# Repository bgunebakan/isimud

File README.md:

# Isimud
Sattellite modem control software and web application

# v2
Isimud v2 created with JAVA and Netbeans 8.0.2

# Libraries
 - Commons Cli 1.2
 - Pi4j

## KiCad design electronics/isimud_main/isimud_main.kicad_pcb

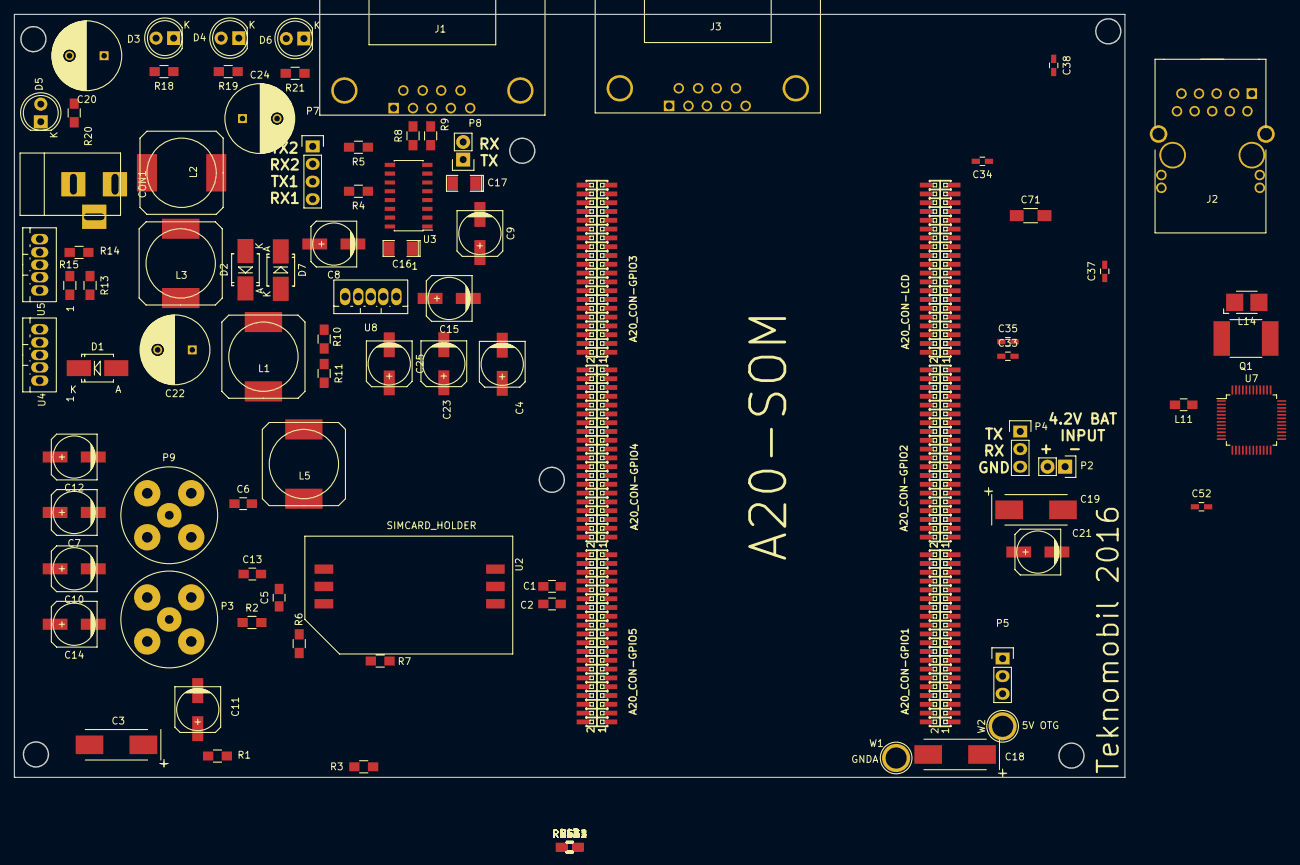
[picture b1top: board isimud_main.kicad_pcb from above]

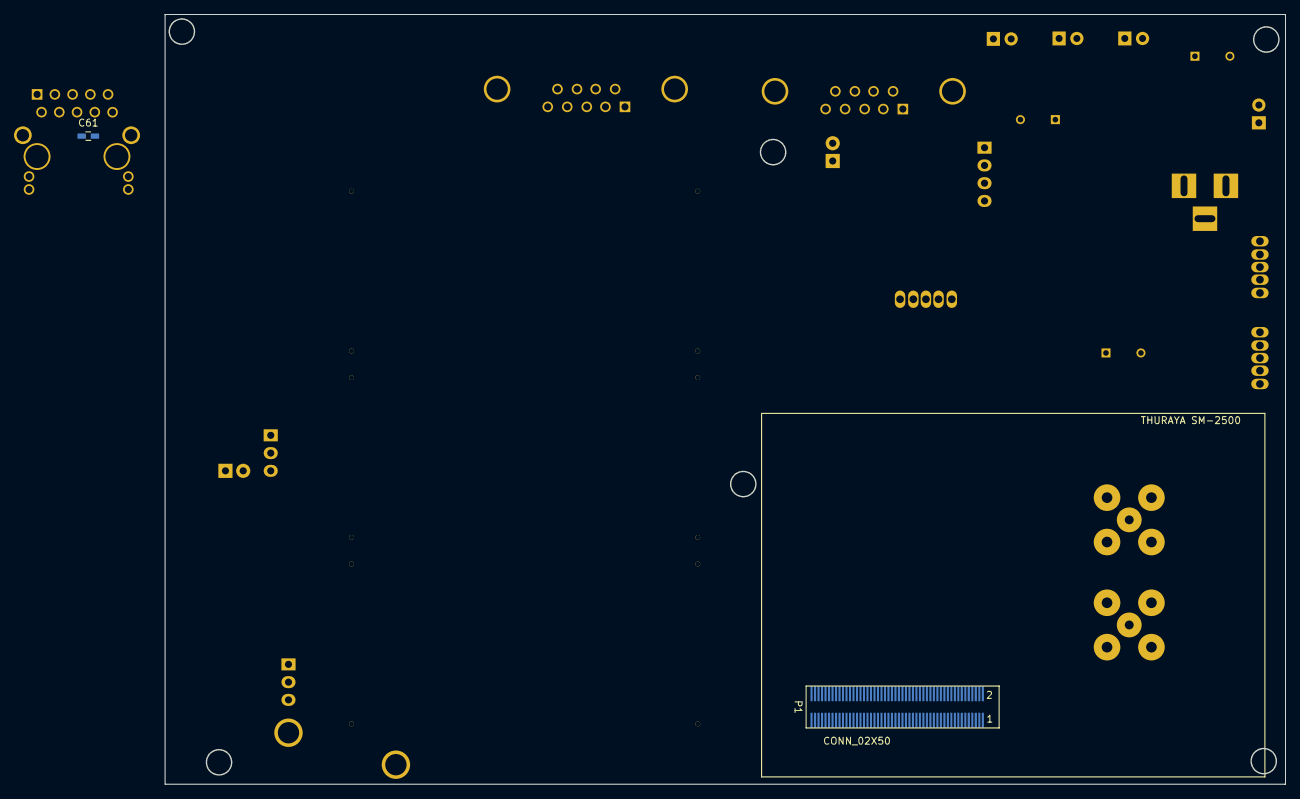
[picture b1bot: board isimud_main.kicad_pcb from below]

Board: 2 copper layers, 160.3 x 110.1 mm, 129 parts (2 on the bottom side), 115 nets, no tracks yet.

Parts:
C1, C2, C5: 33pF; C_0805_HandSoldering
C3: 33uF 16V; TantalC_SizeD_EIA-7343_HandSoldering
C4: 1uF 16V; c_elec_6.3x5.8
C6, C13: 100nF; C_0805_HandSoldering
C7, C10, C11, C12, C14: 47uF 16V; c_elec_6.3x5.8
C8, C9: 1uF; c_elec_6.3x5.8
C15: 100uF; c_elec_6.3x5.8
C16, C17: 1uF; SMD-1206_Pol
C18: 10uF; TantalC_SizeD_EIA-7343_HandSoldering
C19: 22uF 6.3v; TantalC_SizeD_EIA-7343_HandSoldering
C20, C22, C24: 1000uF 16V; C_Radial_D10_L16_P5
C21, C23, C25: 220uF 16V; c_elec_6.3x5.8
C33, C37, C48, C52, C53: 22uF/6.3V; C_0603_HandSoldering
C34, C35, C38, C41, C43, C50, C51, C54, C55, C56, C57, C58, C59, C61: 100nF; C_0603_HandSoldering
C42, C65: NA; C_0603_HandSoldering
C62, C64: 27pF; C_0603_HandSoldering
C71: 1nF/2kV/X7R/1206; C_1206_HandSoldering
CON1: 12V DC; BARREL_JACK
D1, D2, D7: 1N5822; SMB_Handsoldering
D3: SAT_ON; LED-5MM
D4: GPS_ON; LED-5MM
D5: PWR_ON; LED-5MM
D6: STATUS; LED-5MM
J1, J3: DB9; DB9FC
J2: TM211Q01FM22
L1, L2, L3, L5: 100uH; SELF-WE-PD-XXL
L11, L12, L13: FB0805/600R/2A; C_0805_HandSoldering
L14: 4.7uH/1.15A/DCR<0.1R/CD43; Inductor_1212
P1: CONN_02X50; BB-2X50-SMD
P2: LIPO_BAT; Socket_Strip_Straight_1x02
P3: SAT MODULE GPS; bnc-ci
P4: UART_0; Pin_Header_Straight_1x03
P5: UART_4; Pin_Header_Straight_1x03
P7: RS232-UART; Pin_Header_Straight_1x04
P8: RS232-2; Pin_Header_Straight_1x02
P9: AKTIF GPS ANTEN; bnc-ci
Q1: E4SB25.000F20E15(25MHz/20pF/20ppm/5x3.2mm); C_2220_HandSoldering
R1, R2, R8, R9, R11: 0R; R_0805_HandSoldering
R3: 10k; R_0805_HandSoldering
R4, R5: 2k2; R_0805_HandSoldering
R6, R7: 330; R_0805_HandSoldering
R10: NA; R_0805_HandSoldering
R13, R14: 1k2; R_0805_HandSoldering
R15: 1k; R_0805_HandSoldering
R18, R19, R20, R21: 220R; R_0805_HandSoldering
R40: 10K; R_0603_HandSoldering
R41, R42, R66: 22R; R_0603_HandSoldering
R43: 10k; R_0603_HandSoldering
R44, R57, R60, R64: NA; R_0603_HandSoldering
R47, R49, R61: 1K; R_0603_HandSoldering
R48, R59, R62: 4K7; R_0603_HandSoldering
R52: 2.49k/1%; R_0603_HandSoldering
R63: 1k; R_0603_HandSoldering
R65: NA(4.7k); R_0603_HandSoldering
RM4G1, RM4G2, RM4G3: R; R_0603_HandSoldering
RM5G1, RM5G2, RM5G3, RM5G4: RA1206_(4X0603)_4B8_22R; R_0603_HandSoldering
U1: SOM-A20; A20-SOM
U2: SIMCARD_HOLDER; SIMCARD
U3: MAX232; SOIC-16_3.9x9.9mm_Pitch1.27mm
U4, U8: LM2576-5V; Pentawatt_Neutral_Straight_Vertical_TO220-5-T05A
U5: LM2576; Pentawatt_Neutral_Straight_Vertical_TO220-5-T05A
U7: RTL8211CL-GR; LQFP-48_7x7mm_Pitch0.5mm
W1: GNDA; 1pin
W2: 5V OTG; 1pin

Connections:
+3V3: L11.2, L12.2, L13.2, R47.2, R48.2, R49.2, R62.2, RM4G1.2, RM4G2.2, RM4G3.2, U1.3-3, U1.4-3, U1.6-3
+5V: C7.1, C10.1, C12.1, C14.1, C16.2, C18.1, P1.65, P1.93, P1.94, P1.95, P1.96, P1.97, P1.98, P1.99, P1.100, R1.2, R3.2, U1.1-1, U1.3-1, U1.4-1, U1.6-1, U3.16
+5VD: C24.1, C25.1, L2.2, U8.4
+6V: C3.1, C4.1, C22.1, C23.1, L3.2, P1.73, P1.75, P1.77, P1.79, P1.81, R13.2
+12V: C15.1, CON1.1, U4.1, U5.1, U8.1
+BATT: C19.1, P2.2, U1.2-3
/THURAYA_RX: P1.24, R7.2
/THURAYA_TX: P1.22, R6.2
CLK125: R66.2, U1.2-38
EMDIO: R49.1, U7.31
EPHY-RST#: R64.1, U1.2-40
ERXCK: R42.2, U1.2-33
ERXD0: RM5G4.2, U1.2-23
ERXD1: RM5G3.2, U1.2-25
ERXD2: RM5G2.2, U1.2-27
ERXD3: RM5G1.2, U1.2-29
ERXDV: R41.2, U1.2-31
ETXCK: R10.1, R11.1, U7.22
ETXD0: U1.2-24, U7.23
ETXD1: U1.2-26, U7.24
ETXD2: U1.2-28, U7.25
ETXD3: U1.2-30, U7.26
ETXEN: U1.2-32, U7.27
GND: C1.2, C2.2, C3.2, C4.2, C5.2, C7.2, C10.2, C12.2, C14.2, C15.2, C17.1, C18.2, C19.2, C20.2, C21.2, C22.2, C23.2, C24.2, C25.2, C33.1, C34.1, C35.1, C37.1, C38.1, C41.1, C42.1, C43.1, C48.1, C50.1, C51.1, C52.1, C53.1, C54.1, C55.1, C56.1, C57.1, C58.1, C59.2, C61.2, C62.1, C64.1, C65.1, C71.1, CON1.2, CON1.3, D1.2, D2.2, D3.1, D4.1, D5.1, D6.1, D7.2, J1.5, J2.10, J3.5, P1.28, P1.35, P1.50, P1.67, P1.68, P1.69, P1.70, P1.76, P1.82, P1.83, P1.85, P1.86, P1.87, P1.88, P1.89, P1.90, P1.91, P1.92, P2.1, P4.3, P5.3, R2.2, R15.1, R40.2, R44.1, R52.1, R59.1, R60.2, R61.1, R65.2, U1.1-2, U1.2-2, U1.2-4, U1.4-2, U1.5-2, U1.6-2, U1.6-4, U2.4, U3.15, U4.3, U4.5, U5.3, U5.5, U7.7, U7.12, U7.20, U7.33, U7.47, U8.3, U8.5
GNDA: U1.1-4, W1.1
GPS_LED: R19.1, U1.5-9
unnamed: C1.1, P1.62, U2.2
unnamed: C2.1, P1.60, U2.3
unnamed: C5.1, P1.58, U2.6
unnamed: C8.1, U3.1
unnamed: C8.2, U3.3
unnamed: C9.1, U3.4
unnamed: C9.2, U3.5
unnamed: C6.2, C11.1, L5.1, R1.1
unnamed: C6.1, C11.2, P3.2, P9.2, R2.1
unnamed: C13.1, P3.1
unnamed: C13.2, L5.2, P9.1
unnamed: C16.1, U3.2
unnamed: C17.2, U3.6
unnamed: C33.2, C34.2, C35.2, L11.1, U7.6, U7.41
unnamed: C37.2, C38.2, C41.2, C43.2, L12.1, U7.15, U7.21, U7.37
unnamed: C42.2, R42.1, U7.19
unnamed: C48.2, C50.2, C51.2, L13.1, U7.44, U7.45
unnamed: C52.2, C53.2, C54.2, C55.2, C56.2, C57.2, C58.2, L14.2, U7.3, U7.10, U7.28, U7.36, U7.40
unnamed: C59.1, J2.5
unnamed: C61.1, J2.6
unnamed: C62.2, Q1.1, U7.42
unnamed: C64.2, Q1.2, U7.43
unnamed: C65.2, R57.2, R63.2, R64.2, U7.29
unnamed: C71.2, J2.SH1, J2.SH2
unnamed: D1.1, L1.1, U4.2
unnamed: D2.1, L3.1, U5.2
unnamed: D3.2, R18.2
unnamed: D4.2, R19.2
unnamed: D5.2, R20.2
unnamed: D6.2, R21.2
unnamed: D7.1, L2.1, U8.2
unnamed: J1.2, R8.2
unnamed: J1.3, R9.2
unnamed: J2.1, U7.1
unnamed: J2.2, U7.2
unnamed: J2.3, U7.4
unnamed: J2.4, U7.5
unnamed: J2.7, U7.8
unnamed: J2.8, U7.9
unnamed: J2.9, U7.11
unnamed: J2.11, R59.2, U7.35
unnamed: J2.12, R61.2
unnamed: J2.13, R47.1
unnamed: J2.14, R48.1, U7.34
unnamed: L14.1, U7.48
unnamed: P1.64, U2.1
unnamed: P7.3, U3.10
unnamed: P7.4, R5.2
unnamed: P8.1, U3.7
unnamed: P8.2, U3.8
unnamed: R4.1, U3.12
unnamed: R5.1, U3.9
unnamed: R8.1, U3.14
unnamed: R9.1, U3.13
unnamed: R10.2, U1.2-34
unnamed: R11.2, U1.2-36
unnamed: R13.1, R14.1
unnamed: R14.2, R15.2, U5.4
unnamed: R40.1, R41.1, U7.13
unnamed: R43.1, R57.1
unnamed: R43.2, R44.2, U7.39
unnamed: R52.2, U7.46
unnamed: R60.1, R62.1, U7.38
unnamed: R65.1, RM4G3.1, RM5G3.1, U7.16
unnamed: R66.1, U7.32
unnamed: RM4G1.1, RM5G1.1, U7.18
unnamed: RM4G2.1, RM5G2.1, U7.17
unnamed: RM5G4.1, U7.14
unnamed: U1.1-5, W2.1
PG6: J3.1, U1.5-13
PG8: J3.2, U1.5-17
PG9: J3.3, U1.5-19
PG10: J3.4, U1.5-21
PG11: J3.6, U1.5-23
PWR_LED: C20.1, C21.1, L1.2, R20.1, U1.2-1, U4.4
RESET_N: R63.1, U1.4-40
SAT_LED: R18.1, U1.5-7
SAT_OFF: P1.59, U1.5-5
SAT_ON: P1.57, U1.5-1
SAT_RST: P1.51, R3.1, U1.5-3
STATUS_LED: R21.1, U1.3-7
UART0_RX: P4.2, U1.2-22
UART0_TX: P4.1, U1.2-21
UART3_RX: P7.2, R4.2, U1.5-15
UART3_TX: P7.1, U1.3-5, U3.11
UART4_RX: P5.2, U1.1-9
UART4_TX: P5.1, U1.1-11
UART6_RX: R6.1, U1.4-28
UART6_TX: R7.1, U1.4-27

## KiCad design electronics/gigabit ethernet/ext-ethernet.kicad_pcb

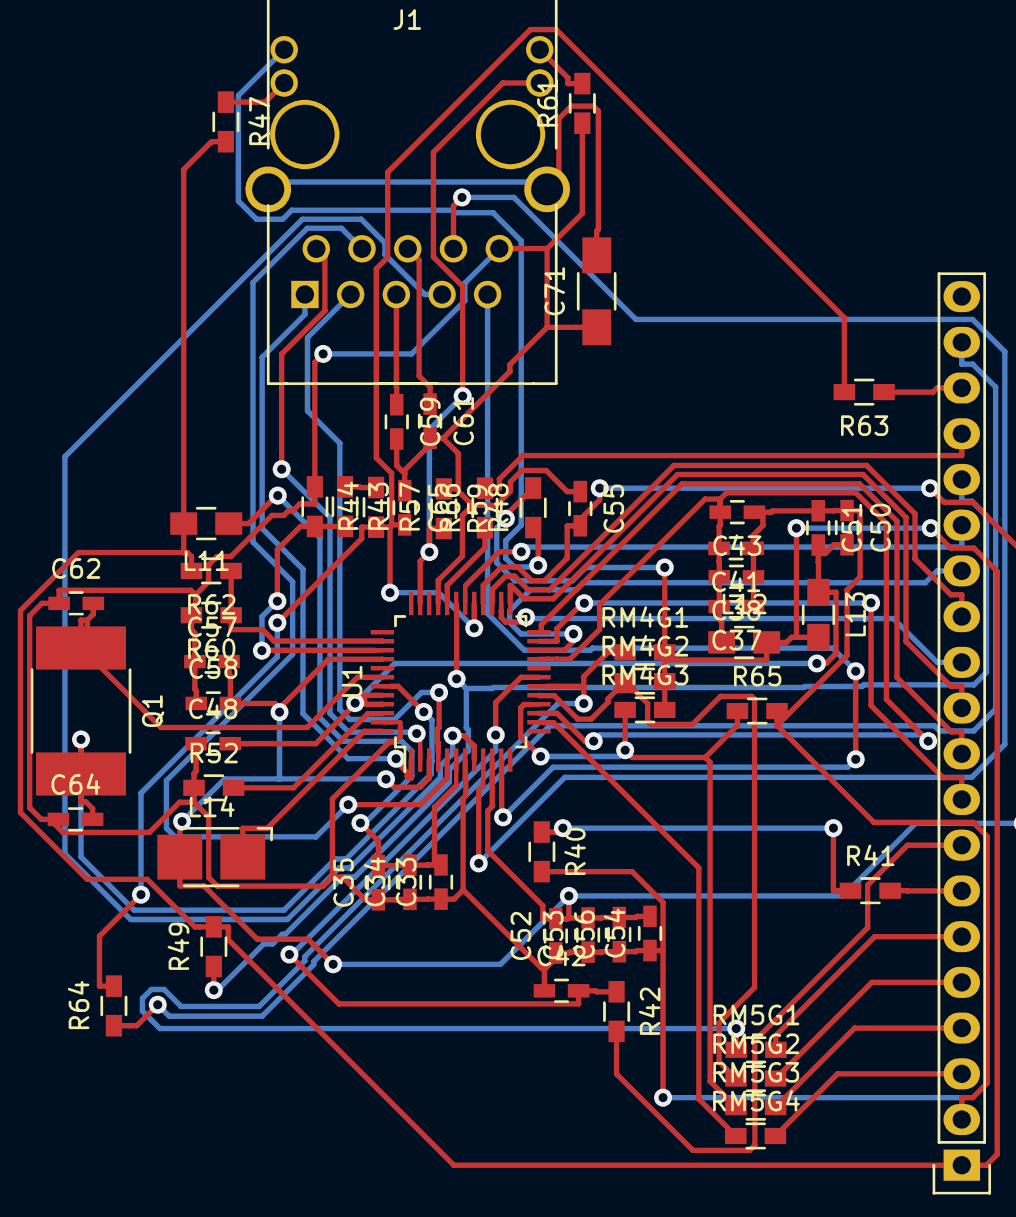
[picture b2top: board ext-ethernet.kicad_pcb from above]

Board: 2 copper layers, 57 parts (0 on the bottom side), 52 nets.

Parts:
C33, C37, C48, C52, C53: 22uF/6.3V; C_0603_HandSoldering
C34, C35, C38, C41, C43, C50, C51, C54, C55, C56, C57, C58, C59, C61: 100nF; C_0603_HandSoldering
C42, C65: NA; C_0603_HandSoldering
C62, C64: 27pF; C_0603_HandSoldering
C71: 1nF/2kV/X7R/1206; C_1206_HandSoldering
J1: TM211Q01FM22
L11, L12, L13: FB0805/600R/2A; C_0805_HandSoldering
L14: 4.7uH/1.15A/DCR<0.1R/CD43; Inductor_1212
P1: CONN_01X20; Pin_Header_Straight_1x20
Q1: E4SB25.000F20E15(25MHz/20pF/20ppm/5x3.2mm); C_2220_HandSoldering
R40: 10K; R_0603_HandSoldering
R41, R42, R66: 22R; R_0603_HandSoldering
R43: 10k; R_0603_HandSoldering
R44, R57, R60, R64: NA; R_0603_HandSoldering
R47, R49, R61: 1K; R_0603_HandSoldering
R48, R59, R62: 4K7; R_0603_HandSoldering
R52: 2.49k/1%; R_0603_HandSoldering
R63: 1k; R_0603_HandSoldering
R65: NA(4.7k); R_0603_HandSoldering
RM4G1, RM4G2, RM4G3: R; R_0603_HandSoldering
RM5G1, RM5G2, RM5G3, RM5G4: RA1206_(4X0603)_4B8_22R; R_0603_HandSoldering
U1: RTL8211CL-GR; LQFP-48_7x7mm_Pitch0.5mm

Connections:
+3V3: L11.2, L12.2, L13.2, P1.1, R47.2, R48.2, R49.2, R62.2, RM4G1.2, RM4G2.2, RM4G3.2
GND: C33.1, C34.1, C35.1, C37.1, C38.1, C41.1, C42.1, C43.1, C48.1, C50.1, C51.1, C52.1, C53.1, C54.1, C55.1, C56.1, C57.1, C58.1, C59.2, C61.2, C62.1, C64.1, C65.1, C71.1, J1.10, P1.2, R40.2, R44.1, R52.1, R59.1, R60.2, R61.1, R65.2, U1.7, U1.12, U1.20, U1.33, U1.47
unnamed: C33.2, C34.2, C35.2, L11.1, U1.6, U1.41
unnamed: C37.2, C38.2, C41.2, C43.2, L12.1, U1.15, U1.21, U1.37
unnamed: C42.2, R42.1, U1.19
unnamed: C48.2, C50.2, C51.2, L13.1, U1.44, U1.45
unnamed: C52.2, C53.2, C54.2, C55.2, C56.2, C57.2, C58.2, L14.2, U1.3, U1.10, U1.28, U1.36, U1.40
unnamed: C59.1, J1.5
unnamed: C61.1, J1.6
unnamed: C62.2, Q1.1, U1.42
unnamed: C64.2, Q1.2, U1.43
unnamed: C65.2, R57.2, R63.2, R64.2, U1.29
unnamed: C71.2, J1.SH1, J1.SH2
unnamed: J1.1, U1.1
unnamed: J1.2, U1.2
unnamed: J1.3, U1.4
unnamed: J1.4, U1.5
unnamed: J1.7, U1.8
unnamed: J1.8, U1.9
unnamed: J1.9, U1.11
unnamed: J1.11, R59.2, U1.35
unnamed: J1.12, R61.2
unnamed: J1.13, R47.1
unnamed: J1.14, R48.1, U1.34
unnamed: L14.1, U1.48
unnamed: P1.3, RM5G4.2
unnamed: P1.4, RM5G3.2
unnamed: P1.5, RM5G2.2
unnamed: P1.6, RM5G1.2
unnamed: P1.7, R41.2
unnamed: P1.8, R42.2
unnamed: P1.9, U1.23
unnamed: P1.10, U1.24
unnamed: P1.11, U1.25
unnamed: P1.12, U1.26
unnamed: P1.13, U1.27
unnamed: P1.14, U1.22
unnamed: P1.15, U1.30
unnamed: P1.16, R49.1, U1.31
unnamed: P1.17, R66.2
unnamed: P1.18, R63.1
unnamed: P1.19, R64.1
unnamed: R40.1, R41.1, U1.13
unnamed: R43.1, R57.1
unnamed: R43.2, R44.2, U1.39
unnamed: R52.2, U1.46
unnamed: R60.1, R62.1, U1.38
unnamed: R65.1, RM4G3.1, RM5G3.1, U1.16
unnamed: R66.1, U1.32
unnamed: RM4G1.1, RM5G1.1, U1.18
unnamed: RM4G2.1, RM5G2.1, U1.17
unnamed: RM5G4.1, U1.14

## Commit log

2015-01-30 github repo created
2015-01-30 some changes
2015-02-09 Isimud v2 created with java.all code rewrite
2015-02-10 tcp and serial communication ok
2015-02-11 last
2015-02-11 index page almost done
2015-02-11 gitignore
2015-02-11 empty commit
2015-02-11 tcp and serial not working
2015-02-21 tcp not working
2015-02-22 moving with new tcp methods
2015-02-22 new branch contains only java
2015-02-22 all done
2015-02-27 log file added
2015-02-28 web interface methods rewritten
2015-03-01 gpio and logs are done
2015-03-02 all functions is working and modbus is almoust done.
2015-03-11 web interface changed to bootable commands
2015-03-11 comm are starting at boot now.well done!
2015-03-13 web changed
2015-03-17 last beta
2015-03-20 web page working_mode solved.serial comm solved
2015-03-20 serial test program
2015-03-21 all done for release
2016-07-17 lots of datasheet and main board schematics
2016-07-20 parts placed on print board
2016-07-24 pcb design is done,last checks for gerber
2016-07-26 new revision for production
2016-07-28 pcb rev.a produced,mechanics design has began
2016-07-28 mechanic design is not finished
2016-07-30 box design is finished
2016-08-03 test 0.1
2016-09-24 REV1.A is done but enc28j60 is not working,go next revision
2016-09-30 moving to revision 2
2016-09-30 shematics is done,pcb routing started
2017-01-13 thuraya datasheets
2019-10-23 Create LICENSE
